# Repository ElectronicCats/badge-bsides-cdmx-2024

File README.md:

# Badge bsides CDMX 2024

## Getting started

1. Connect Badge via USB to your computer.
2. Open the serial port indicated for the badge on your computer through a program such as Arduino IDE, Putty or Screen at 115200 bauds.
3. The badge text should appear in the terminal.

## Tecnologia

- ESP32C6
- Neopixel LEDs
- USB C
- Display OLED
- 2x AA Battery Holder
- Shitty Addon Connector

## Gratitude
Do you want to say thank you? Tag these companies on social networks and show them your badge, thanks to them it is possible

- [HSBC](https://www.hsbc.com.mx/)
- [ElectronicCats](https://electroniccats.com/)
- [Bsides CDMX](https://bsidescdmx.org/)

## License

Electronic Cats invests time and resources providing this open source design, please support Electronic Cats and open-source hardware by purchasing products from Electronic Cats!

Designed by Electronic Cats.

Hardware released under an CERN Open Hardware Licence v1.2. See the LICENSE_HARDWARE file for more information.

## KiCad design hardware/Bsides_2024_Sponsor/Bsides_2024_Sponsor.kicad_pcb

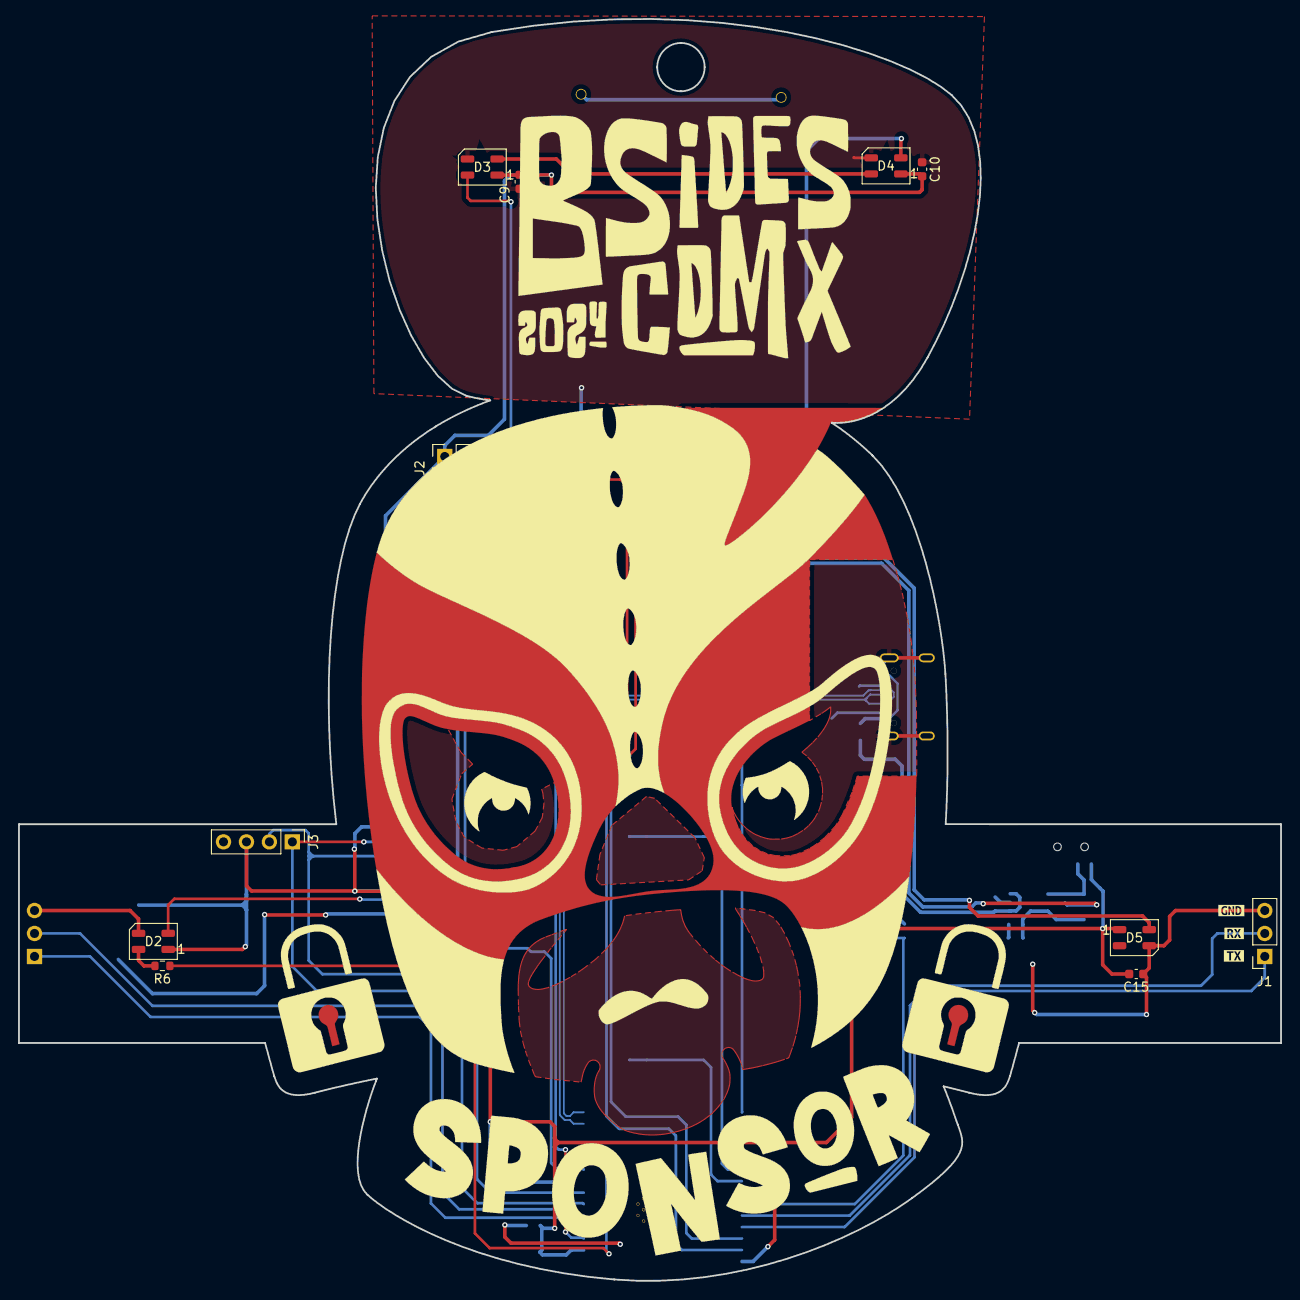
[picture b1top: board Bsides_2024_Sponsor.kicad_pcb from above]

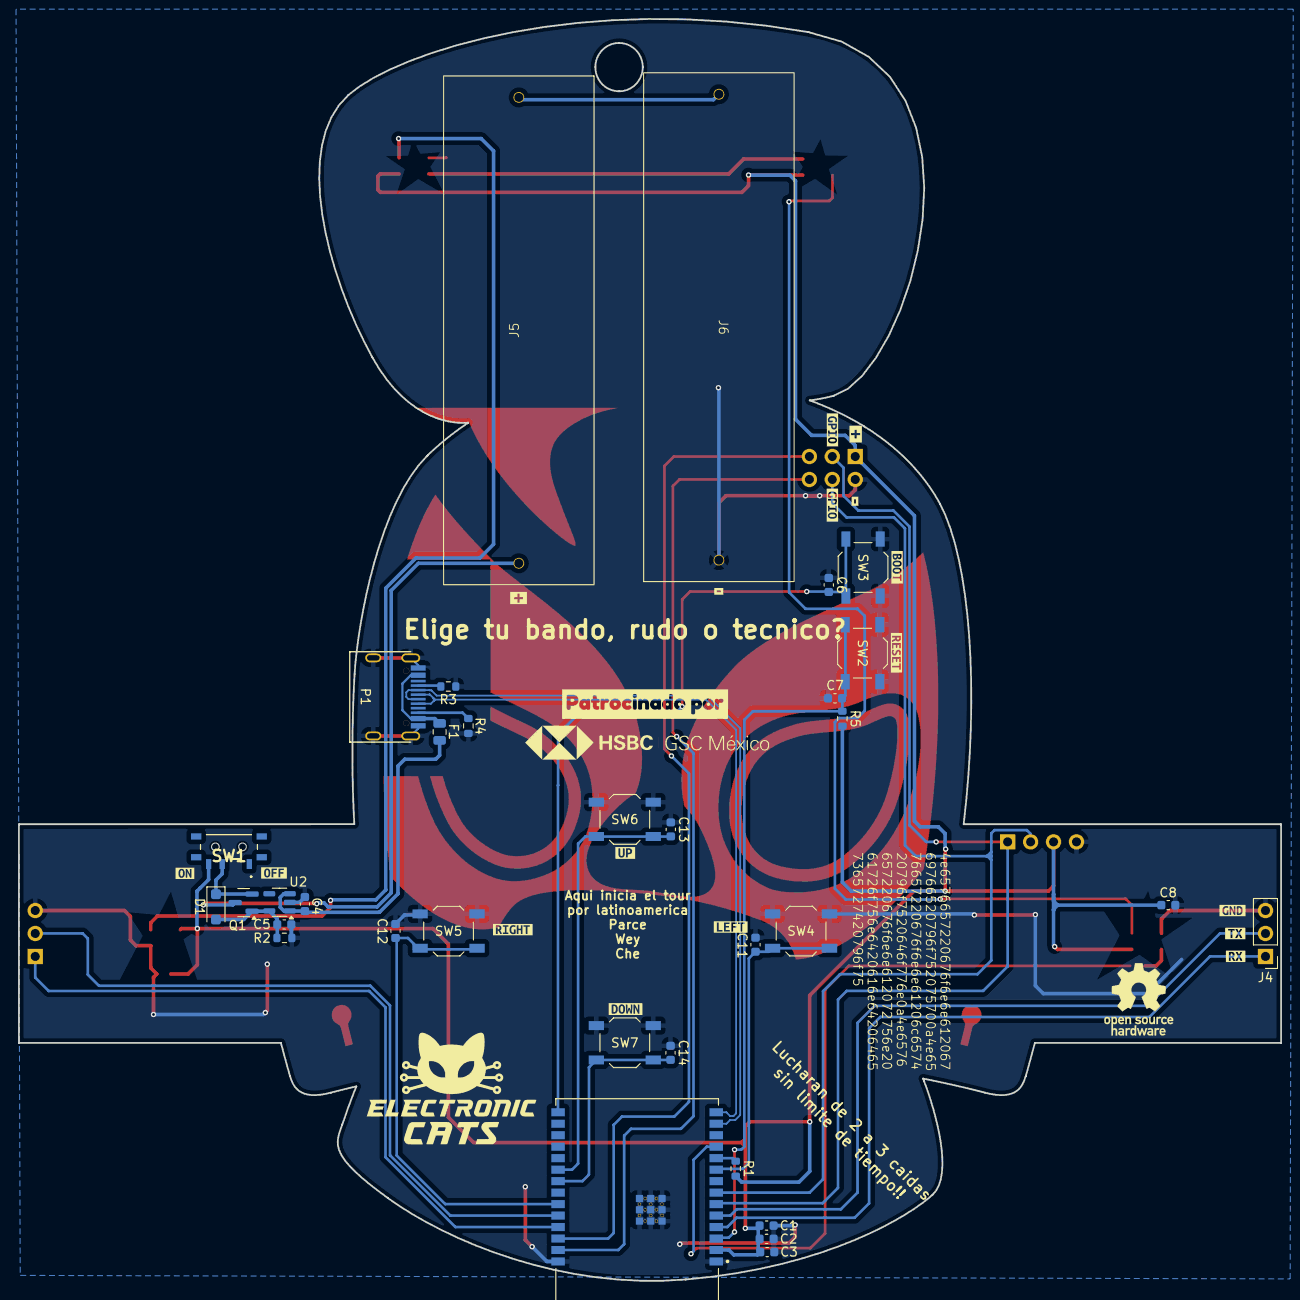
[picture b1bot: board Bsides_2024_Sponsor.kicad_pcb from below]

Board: 2 copper layers, 139.6 x 139.6 mm, 66 parts (51 on the bottom side), 32 nets.

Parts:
C1: 1uF; C_0603_1608Metric
C2, C3, C4, C5: 10uF; C_0603_1608Metric
C6, C7, C8, C9, C10, C11, C12, C13, C14, C15: 0.1uF; C_0603_1608Metric
D1: MBR120; D_SOD-123F
D2, D3, D4, D5: WS2812B; LED_WS2812B-Mini_PLCC4_3.5x3.5mm
F1: 0.75A; Fuse_0805_2012Metric
J1: Serial_IN; PinSocket_1x03_P2.54mm_Vertical
J2: Add_On; PinSocket_2x03_P2.54mm_Vertical
J3: OLED; Display OLED 128 x32
J4: Serial_OUT; PinHeader_1x03_P2.54mm_Vertical
J5, J6: Battery; BH-AA-A1AJ020
P1: USB_C_Plug_USB2.0; C393939
Q1: DMG3415U-7; SOT-23
R1: 3.3K; R_0603_1608Metric
R2: 100K; R_0603_1608Metric
R3, R4: 5k1; R_0603_1608Metric
R5: 10K; R_0603_1608Metric
R6: 470; R_0603_1608Metric
Ref**: Val**; Badge_Sponsor_Bsides_2024_CDMX
SW1: ON; MSK12C02
SW2, SW4, SW6: RESET; SW_SPST_TL3342
SW3: BOOT; SW_SPST_TL3342
SW5, SW7: SW_SPST_TL3342
U1: ESP32-C6-WROOM-1-N4; XCVR_ESP32-C6-WROOM-1-N8
U2: AP2112K-3.3; SOT-23-5
kibuzzard-666B5A62, kibuzzard-666B5A62#2: G***; kibuzzard-666B5A62
kibuzzard-666B5A91, kibuzzard-666B5A91#2: G***; kibuzzard-666B5A91
kibuzzard-666B5AA1, kibuzzard-666B5AA1#2: G***; kibuzzard-666B5AA1
kibuzzard-666B5BCA, kibuzzard-666B5BCA#2: G***; kibuzzard-666B5BCA
kibuzzard-666B5C0A, kibuzzard-666B5C0A#2: G***; kibuzzard-666B5C0A
kibuzzard-666B55CA: G***; kibuzzard-666B55CA
kibuzzard-666B327A: G***; kibuzzard-666B327A
kibuzzard-666B3243: G***; kibuzzard-666B3243
kibuzzard-666B3258: G***; kibuzzard-666B3258
kibuzzard-666C8E87: G***; kibuzzard-666C8E87
kibuzzard-666C63C4: G***; kibuzzard-666C63C4
kibuzzard-666C631C: G***; kibuzzard-666C631C
kibuzzard-666C633C: G***; kibuzzard-666C633C
kibuzzard-666C639C: G***; kibuzzard-666C639C
kibuzzard-666CA778: G***; kibuzzard-666CA778
kibuzzard-666CA782: G***; kibuzzard-666CA782

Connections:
+BATT: J5.2, Q1.3 (D)
/BOOT: C6.2, SW3.2, U1.15 (IO9)
/D+: P1.A6 (D+), U1.14 (IO13)
/D-: P1.A7 (D-), U1.13 (IO12)
/DOWN: C14.2, SW7.2, U1.21 (IO23)
/EN: C7.2, R5.1, SW2.2, U1.3 (EN)
/GPIO2: J2.6, U1.27 (IO2)
/GPIO3: J2.5, U1.26 (IO3)
/LEFT: C11.2, SW4.2, U1.9 (IO1)
/PIN: R6.1, U1.11 (IO10)
/RIGHT: C12.2, SW5.2, U1.23 (IO15)
/RX: J1.2, U1.24 (RXD0)
/RX1: J4.1, U1.4 (IO4)
/SCL: J2.4, J3.2, U1.7 (IO7)
/SDA: J2.3, J3.1, U1.6 (IO6)
/TX: J1.1, U1.25 (TXD0)
/TX1: J4.2, U1.5 (IO5)
/UP: C13.2, SW6.2, U1.20 (IO22)
/VOUT: C1.1, C2.1, C3.1, C8.2, C9.2, C10.2, C15.2, D2.1 (VDD), D3.1 (VDD), D4.1 (VDD), D5.1 (VDD), J2.1, J3.3, R1.2, R5.2, SW1.3 (A), U1.2 (3V3)
GND: C1.2, C2.2, C3.2, C4.2, C5.2, C6.1, C7.1, C8.1, C9.1, C10.1, C11.1, C12.1, C13.1, C14.1, C15.1, D2.3 (VSS), D3.3 (VSS), D4.3 (VSS), D5.3 (VSS), J1.3, J2.2, J3.4, J4.3, J6.1, P1.A1 (GND), P1.S1 (SHIELD), R2.2, R3.1, R4.1, SW2.1, SW3.1, SW4.1, SW5.1, SW6.1, SW7.1, U1.1 (GND), U1.28 (GND), U1.29 (GND), U1.30 (GND), U1.31 (GND), U1.32 (GND), U1.33 (GND), U1.34 (GND), U1.35 (GND), U1.36 (GND), U1.37 (GND), U2.2 (GND)
unnamed: C5.1, D1.2 (A), Q1.1 (G), R2.1, U2.5 (VOUT)
unnamed: D1.1 (K), Q1.2 (S), SW1.2 (B)
unnamed: D2.4 (DIN), R6.2
unnamed: D2.2 (DOUT), D3.4 (DIN)
unnamed: D3.2 (DOUT), D4.4 (DIN)
unnamed: D4.2 (DOUT), D5.4 (DIN)
unnamed: F1.1, P1.A4 (VBUS)
unnamed: J5.1, J6.2
unnamed: P1.A5 (CC), R3.2
unnamed: P1.B5 (VCONN), R4.2
unnamed: R1.1, U1.10 (IO8)
VBUS: C4.1, F1.2, U2.1 (VIN), U2.3 (EN)

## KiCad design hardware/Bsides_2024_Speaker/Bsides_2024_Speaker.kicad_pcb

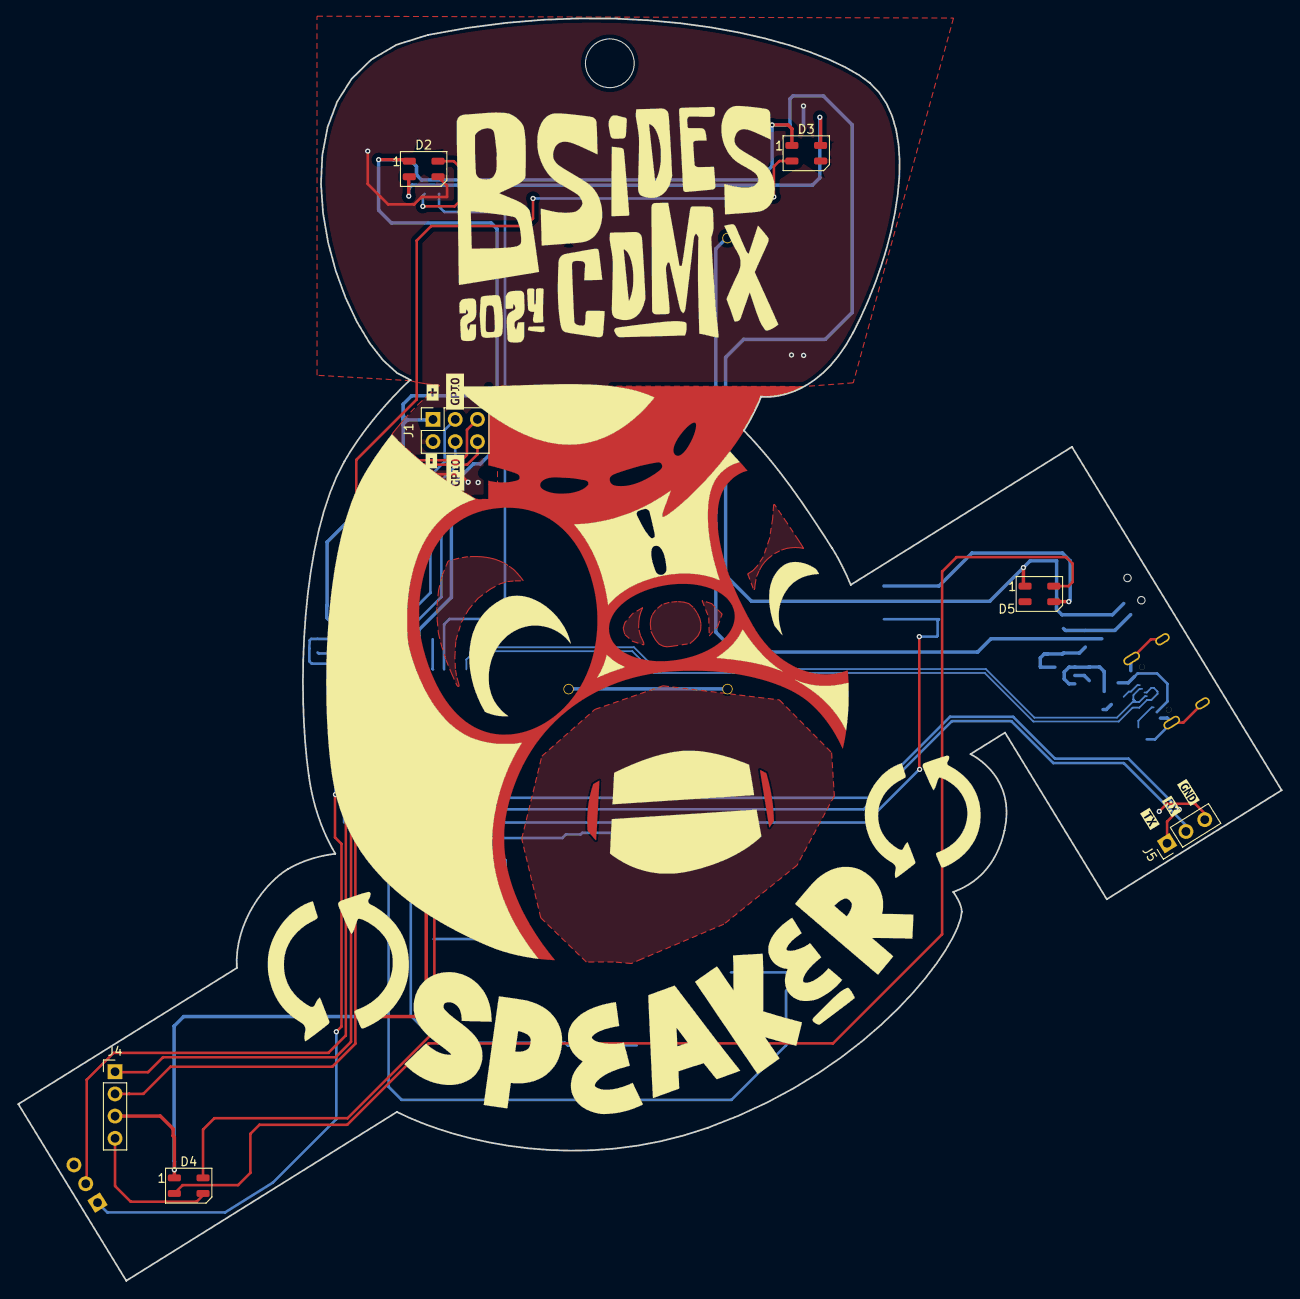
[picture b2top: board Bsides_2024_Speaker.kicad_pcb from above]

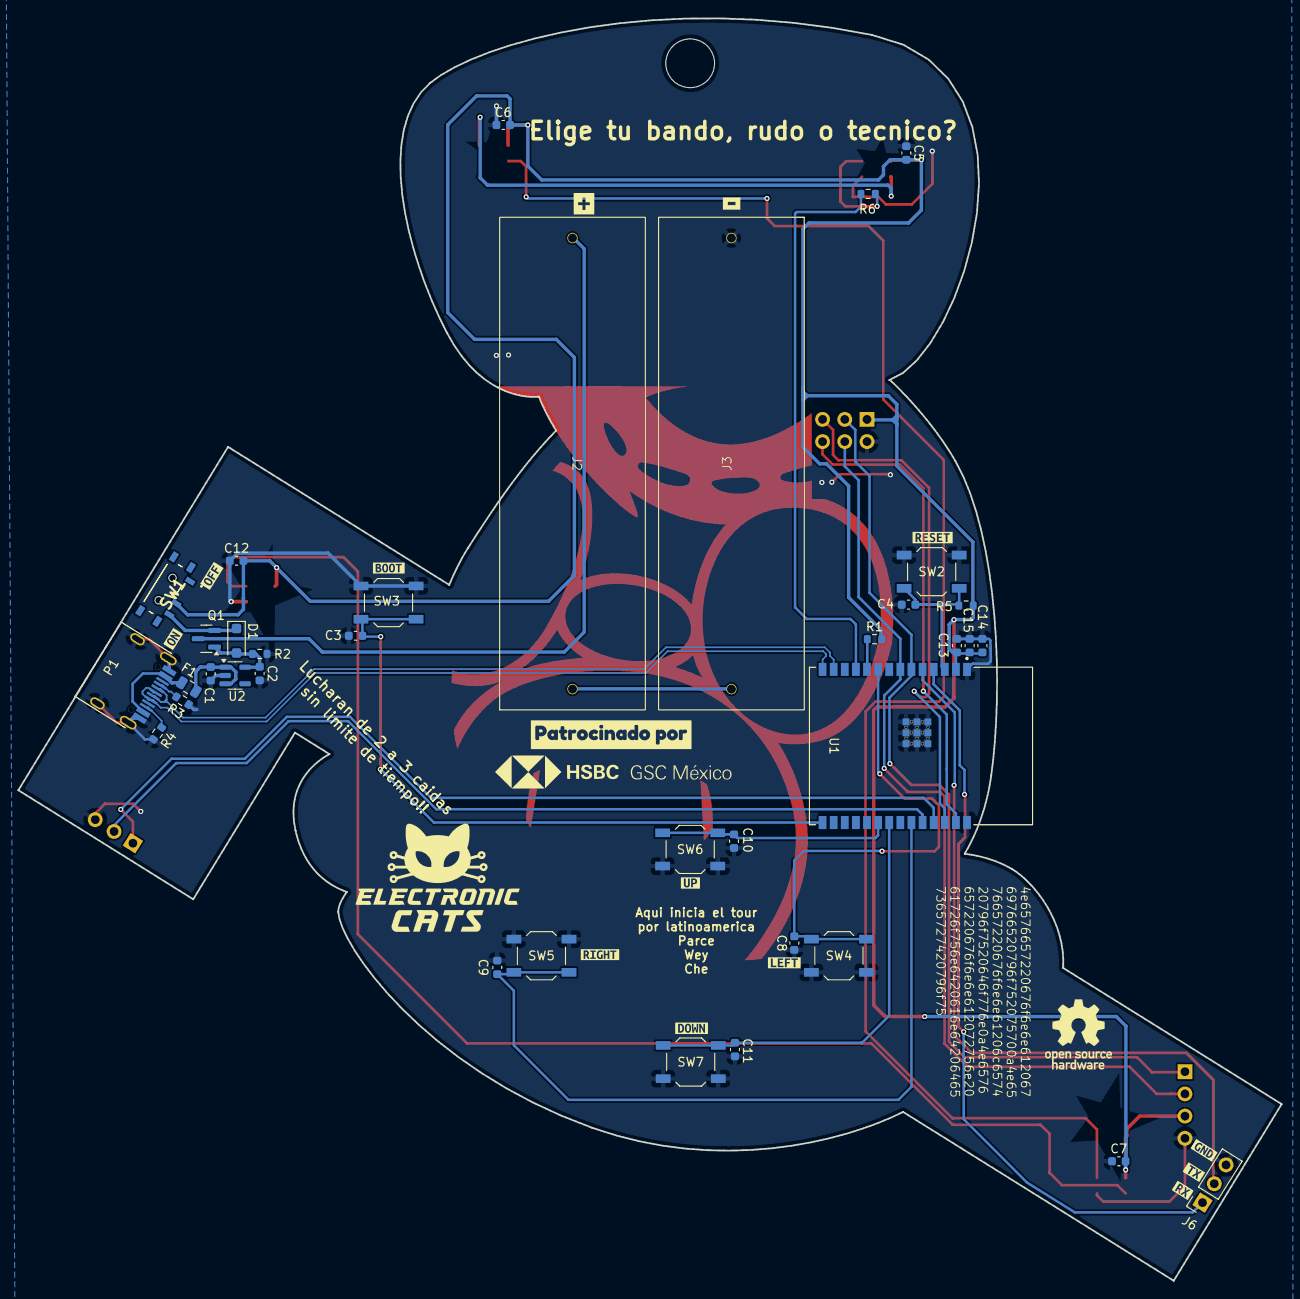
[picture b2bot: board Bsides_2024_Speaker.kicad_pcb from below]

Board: 2 copper layers, 144.4 x 144.3 mm, 66 parts (51 on the bottom side), 32 nets.

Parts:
C1, C2, C14, C15: 10uF; C_0603_1608Metric
C3, C4, C5, C6, C7, C8, C9, C10, C11, C12: 0.1uF; C_0603_1608Metric
C13: 1uF; C_0603_1608Metric
D1: MBR120; D_SOD-123F
D2, D3, D4, D5: WS2812B; LED_WS2812B-Mini_PLCC4_3.5x3.5mm
F1: 0.75A; Fuse_0805_2012Metric
J1: Add_On; PinSocket_2x03_P2.54mm_Vertical
J2, J3: Battery; BH-AA-A1AJ020
J4: OLED; Display OLED 128 x32
J5: Serial_IN; PinHeader_1x03_P2.54mm_Vertical
J6: Serial_OUT; PinSocket_1x03_P2.54mm_Vertical
P1: USB_C_Plug_USB2.0; C393939
Q1: DMG3415U-7; SOT-23
R1: 3.3K; R_0603_1608Metric
R2: 100K; R_0603_1608Metric
R3, R4: 5k1; R_0603_1608Metric
R5: 10K; R_0603_1608Metric
R6: 470; R_0603_1608Metric
Ref**: Val**; Badge_Speaker_Bsides_2024_CDMX
SW1: ON; MSK12C02
SW2, SW4, SW5, SW6, SW7: SW; SW_SPST_TL3342
SW3: BOOT; SW_SPST_TL3342
U1: ESP32-C6-WROOM-1-N4; XCVR_ESP32-C6-WROOM-1-N8
U2: AP2112K-3.3; SOT-23-5
kibuzzard-666B5A62, kibuzzard-666B5A62#2: G***; kibuzzard-666B5A62
kibuzzard-666B5A91, kibuzzard-666B5A91#2: G***; kibuzzard-666B5A91
kibuzzard-666B5AA1, kibuzzard-666B5AA1#2: G***; kibuzzard-666B5AA1
kibuzzard-666B5BCA: G***; kibuzzard-666B5BCA
kibuzzard-666B55CA: G***; kibuzzard-666B55CA
kibuzzard-666B311C: G***; kibuzzard-666B311C
kibuzzard-666B316E: G***; kibuzzard-666B316E
kibuzzard-666B327A: G***; kibuzzard-666B327A
kibuzzard-666B328D: G***; kibuzzard-666B328D
kibuzzard-666B558C: G***; kibuzzard-666B558C
kibuzzard-666B3243: G***; kibuzzard-666B3243
kibuzzard-666B3258: G***; kibuzzard-666B3258
kibuzzard-666C8A00: G***; kibuzzard-666C8A00
kibuzzard-666C8A1B: G***; kibuzzard-666C8A1B
kibuzzard-666C8A24: G***; kibuzzard-666C8A24
kibuzzard-666C8A46: G***; kibuzzard-666C8A46
kibuzzard-666C8E87: G***; kibuzzard-666C8E87
kibuzzard-666C89F7: G***; kibuzzard-666C89F7

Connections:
+BATT: J2.2, Q1.3 (D)
/BOOT: C3.2, SW3.2, U1.15 (IO9)
/D+: P1.A6 (D+), U1.14 (IO13)
/D-: P1.A7 (D-), U1.13 (IO12)
/DOWN: C11.2, SW7.2, U1.21 (IO23)
/EN: C4.2, R5.1, SW2.2, U1.3 (EN)
/GPIO2: J1.6, U1.27 (IO2)
/GPIO3: J1.5, U1.26 (IO3)
/LEFT: C8.2, SW4.2, U1.9 (IO1)
/PIN: R6.1, U1.11 (IO10)
/RIGHT: C9.2, SW5.2, U1.23 (IO15)
/RX: J5.2, U1.24 (RXD0)
/RX1: J6.1, U1.4 (IO4)
/SCL: J1.4, J4.2, U1.7 (IO7)
/SDA: J1.3, J4.1, U1.6 (IO6)
/TX: J5.1, U1.25 (TXD0)
/TX1: J6.2, U1.5 (IO5)
/UP: C10.2, SW6.2, U1.20 (IO22)
/VOUT: C5.2, C6.2, C7.2, C12.2, C13.1, C14.1, C15.1, D2.1 (VDD), D3.1 (VDD), D4.1 (VDD), D5.1 (VDD), J1.1, J4.3, R1.2, R5.2, SW1.2 (B), U1.2 (3V3)
GND: C1.2, C2.2, C3.1, C4.1, C5.1, C6.1, C7.1, C8.1, C9.1, C10.1, C11.1, C12.1, C13.2, C14.2, C15.2, D2.3 (VSS), D3.3 (VSS), D4.3 (VSS), D5.3 (VSS), J1.2, J3.1, J4.4, J5.3, J6.3, P1.A1 (GND), P1.S1 (SHIELD), R2.2, R3.1, R4.1, SW2.1, SW3.1, SW4.1, SW5.1, SW6.1, SW7.1, U1.1 (GND), U1.28 (GND), U1.29 (GND), U1.30 (GND), U1.31 (GND), U1.32 (GND), U1.33 (GND), U1.34 (GND), U1.35 (GND), U1.36 (GND), U1.37 (GND), U2.2 (GND)
unnamed: C2.1, D1.2 (A), Q1.1 (G), R2.1, U2.5 (VOUT)
unnamed: D1.1 (K), Q1.2 (S), SW1.3 (A)
unnamed: D2.4 (DIN), R6.2
unnamed: D2.2 (DOUT), D3.4 (DIN)
unnamed: D3.2 (DOUT), D4.4 (DIN)
unnamed: D4.2 (DOUT), D5.4 (DIN)
unnamed: F1.1, P1.A4 (VBUS)
unnamed: J2.1, J3.2
unnamed: P1.A5 (CC), R3.2
unnamed: P1.B5 (VCONN), R4.2
unnamed: R1.1, U1.10 (IO8)
VBUS: C1.1, F1.2, U2.1 (VIN), U2.3 (EN)

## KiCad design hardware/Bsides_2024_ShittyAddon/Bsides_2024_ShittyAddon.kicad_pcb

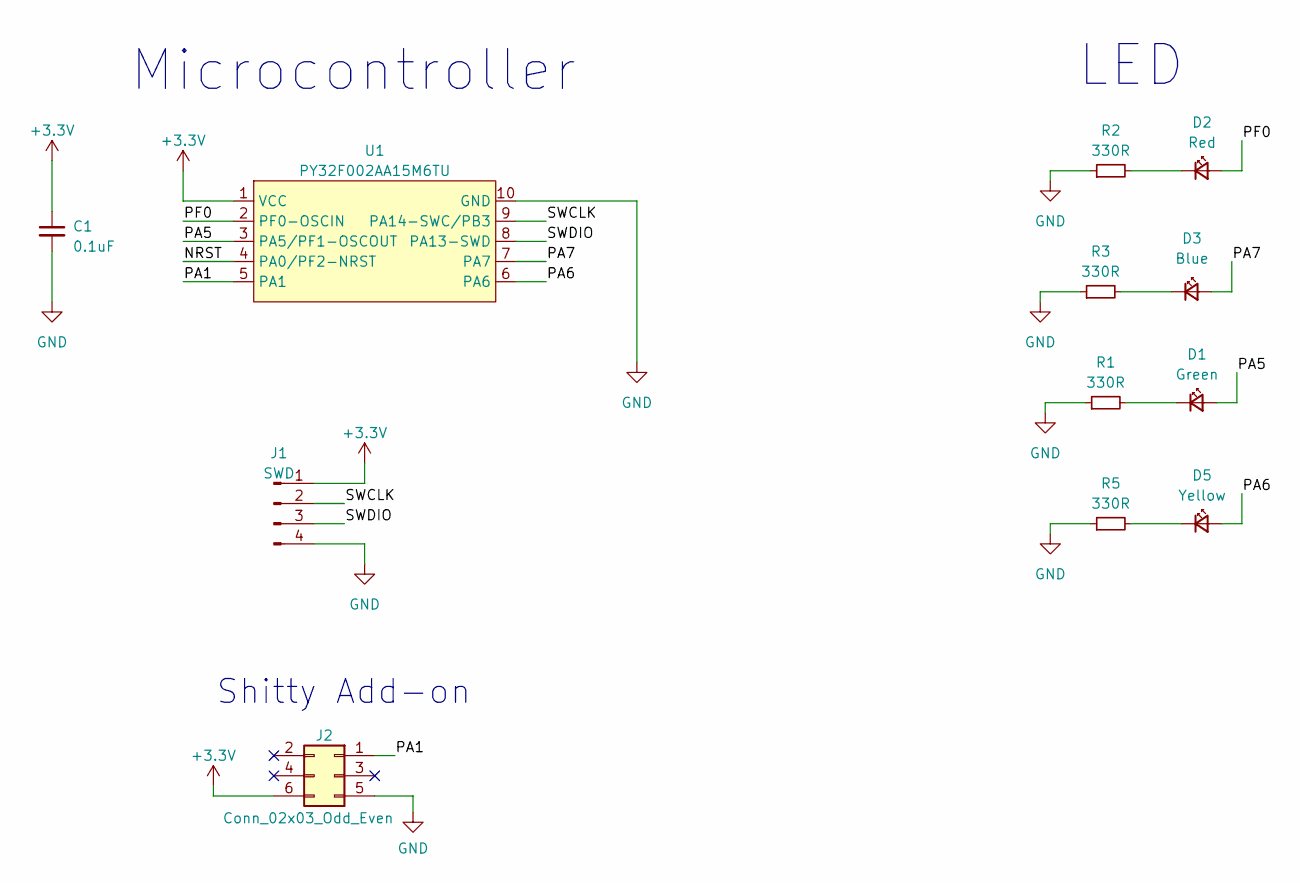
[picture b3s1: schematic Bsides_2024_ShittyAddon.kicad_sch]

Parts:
C1: 0.1uF; C_0805_2012Metric; LCSC# C282732
D1: Green; LED_0805_2012Metric; LCSC# C965815
D2: Red; LED_0805_2012Metric; LCSC# C965812
D3: Blue; LED_0805_2012Metric; LCSC# C205441
D5: Yellow; LED_0805_2012Metric; LCSC# C84261
J1: SWD; PinHeader_1x04_P2.54mm_Vertical
J2: Conn_02x03_Odd_Even; B-2100N06P-B111_CKM; LCSC# C706893
R1, R2, R3, R5: 330R; R_0805_2012Metric; LCSC# C2907321
U1: PY32F002AA15M6TU; PY32F002AA15M; LCSC# C5292058

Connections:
+3.3V: C1.1, J1.1, J2.6, U1.1 (VCC)
/NRST: U1.4 (PA0/PF2-NRST)
/PA1: J2.1, U1.5 (PA1)
/PA5: D1.2 (A), U1.3 (PA5/PF1-OSCOUT)
/PA6: D5.2 (A), U1.6 (PA6)
/PA7: D3.2 (A), U1.7 (PA7)
/PF0: D2.2 (A), U1.2 (PF0-OSCIN)
/SWCLK: J1.2, U1.9 (PA14-SWC/PB3)
/SWDIO: J1.3, U1.8 (PA13-SWD)
GND: C1.2, J1.4, J2.5, R1.1, R2.1, R3.1, R5.1, U1.10 (GND)
unnamed: D1.1 (K), R1.2
unnamed: D2.1 (K), R2.2
unnamed: D3.1 (K), R3.2
unnamed: D5.1 (K), R5.2

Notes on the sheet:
Microcontroller
Shitty Add-on
LED

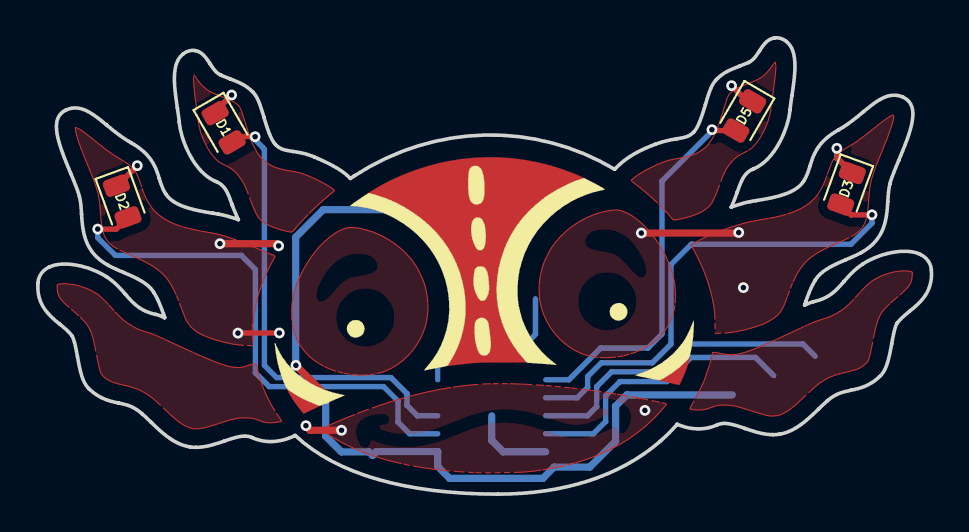
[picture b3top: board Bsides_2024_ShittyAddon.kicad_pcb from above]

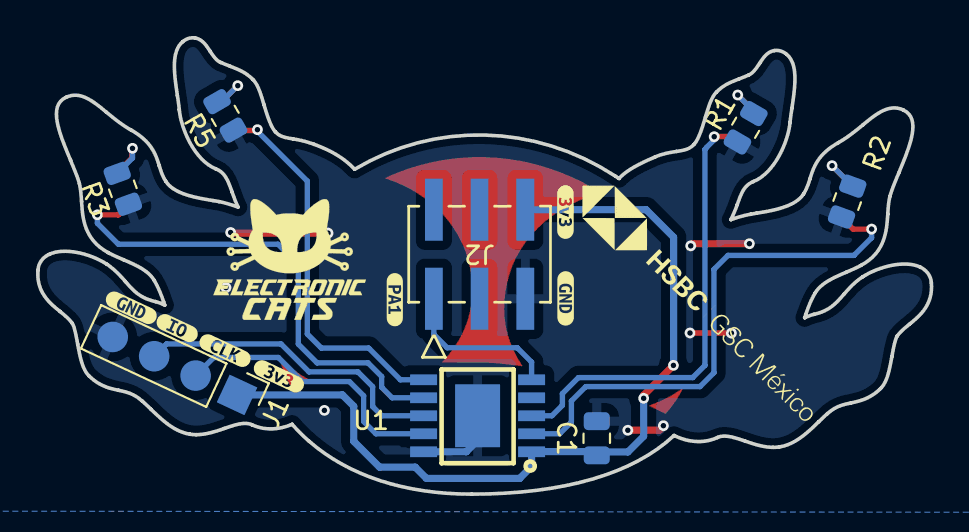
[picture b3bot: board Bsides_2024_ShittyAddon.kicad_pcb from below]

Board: 2 copper layers, 49.7 x 25.4 mm, 20 parts (15 on the bottom side), 13 nets.

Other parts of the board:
Ref**: Val**; Ajolote-bsidescdmx_A
kibuzzard-666C77E0, kibuzzard-666C77E0#2: G***; kibuzzard-666C77E0
kibuzzard-666C787C: G***; kibuzzard-666C787C
kibuzzard-666C7809, kibuzzard-666C7809#2: G***; kibuzzard-666C7809
kibuzzard-666C7823: G***; kibuzzard-666C7823
kibuzzard-666C7874: G***; kibuzzard-666C7874

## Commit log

2024-04-16 feat(Hw):Init_Schematic
2024-04-23 feat(Hw):Added_LED´s_Buttons
2024-04-27 fix(Hw):Changed_raspberry
2024-04-29 feat(hw): add labels schematic
2024-05-07 feat(Hw):Add_Guest_Sponsor_Community_Staff
2024-05-09 feat(Hw):Update_Staff_PCB
2024-05-10 feat(Hw):Init_Floorplan
2024-05-10 feat(Hw):Add_Preview
2024-05-11 feat(Hw):Added_Guest_And_Sponsor_Floorplan_and_3d_Models
2024-05-11 feat(Hw):Update_3d_Model
2024-05-13 feat(Hw):Added_speaker_Badge_Floorplan
2024-05-15 feat: Update README.md
2024-05-20 feat(Hw): Shitty Addon PCB added
2024-05-22 feat(Hw): Start new floorplan
2024-05-27 feat(Hw): Update PCB
2024-05-28 feat(Hw):Update_Route_Speaker
2024-05-28 feat(Hw):Update_PCB_Speaker
2024-05-29 feat(Hw):Update_Floorplan_Sponsor
2024-05-30 feat:(Hw)Update_PCB_Speaker_Sponsor_Staff
2024-06-04 feat(Hw): Update PCB and schematic
2024-06-10 feat: add minino firmware
2024-06-11 First_Route_Speaker
2024-06-11 Revert "Merge branch 'main' of https://github.com/ElectronicCats/badge-bsides-cdmx-2024"
    This reverts commit 844f9cf1141b02d246949023f3a5d84c3d1d6870, reversing
    changes made to df45190e2e7c4c17babbd6f5b24a18277498f0c6.
2024-06-11 feat: adapt interface to 128x32
2024-06-11 feat(Hw): Update schematics
2024-06-11 feat(Hw):Update_Sch_Speaker
2024-06-11 feat(Hw): Update route
2024-06-11 feat(Hw):Update_Staff_Sch_And_PCB
2024-06-12 feat(Hw):First_Route_Staff
2024-06-12 refactor: zboss woking from managed components
2024-06-12 Update route and schematic
2024-06-12 feat(Hw):Update_Route_Sponsor
2024-06-12 feat(Hw):Moved_Buttons_sponsor
2024-06-12 fet(Hw): Update route
2024-06-12 feat(Hw):Moved_Buttons_Speaker
2024-06-13 feat(Hw):Update_Csv_Speaker
2024-06-13 feat(Hw): Update BOM ShittyAddon
2024-06-13 Faet(Hw): Update BOM Speaker
2024-06-13 feat: lobby manager example
2024-06-13 feat(Hw):Update_BOM_Added_Labels
2024-06-13 feat(Hw): Update BOM
2024-06-13 feat(Hw): Update route Speaker and Sponsor
2024-06-14 feat(Hw): Update route Community
2024-06-14 feat(Hw): Labels added
2024-06-14 feat(Hw): Update labels
2024-06-14 feat(Hw):Update_PCB_Community
2024-06-14 feat(Hw):Moved_Battery_Case
2024-06-14 feat(Hw):Update_Guest_SCH_Labels
2024-06-14 feat(Hw):Update_Shitty_Add_On
2024-06-14 feat(Hw): Update schematic and route
2024-06-14 feat(Hw): Update .step
2024-06-14 feat(Hw):Update_Labels_SCH_PCB_Sponsor_And_Staff
2024-06-14 feat(Hw): Move labels
2024-06-14 feat(hw): add labels and logos speaker
2024-06-14 feat: Add games option in menu screens
2024-06-14 feat(hw): add logos staff
2024-06-14 feat(hw): logos sponsor
2024-06-14 feat(hw): add logos guest
2024-06-14 feat(hw): add logos community
2024-06-14 feat(hw): add labels
2024-06-14 feat(hw): add logos shitty addon
2024-06-14 feat(Hw):Update_footprint_badge
2024-06-14 feat(Hw): Update label ShittyAddon
2024-06-14 feat: lobby manager initialized from GUI & deinit added to lobby manager & badge connect
2024-06-15 feat: physical badge connections as conditional for game connection
2024-06-18 refactor: zigbee toggle button & ble spam & wifi deauth bitmaps resized
2024-06-18 refactor: resize of wifi & zigbee bitmaps
2024-06-19 feat: Implement send uart packet
    - Send UART packet
    - Change Zigbee module
    - Add loop menu options
    Note: Bad FCS, requires check the calculation function
2024-06-19 feat: Implement unlock ajolote
2024-06-19 feat: Ajolote animation
    - Fix init logo
2024-06-20 feat: Init DOS
2024-06-20 refactor: add badge connect as a dependency
2024-06-21 feat: handle disconnection events & display events callbacks added
2024-06-21 feat: Implement Wifi config
2024-06-24 fix: badge connect failed to start
2024-06-24 feat: rope game test
2024-06-25 feat: ping attempts implemented
    Forced to be host on lobby manager
2024-06-25 feat: game start from host cmd
2024-06-25 feat: game stops from host
2024-06-25 fix: game exit bug
2024-06-26 feat: DOS app
    - Changes apps
    - Ajo module
2024-06-26 feat: Merge badge connect
2024-06-26 feat: Labels
2024-06-26 fix: add games begin in menu screens module
2024-06-26 feat: create a bar bitmap
2024-06-26 feat(Fw): ShittyAddon firmware added
2024-06-26 chore: remove clean
2024-06-26 chore: enable log master level
2024-06-27 feat: game over event & send game update fixed
2024-06-27 chore: add temporarily lck files
2024-06-27 chore: add configuration rules for minino and badges pins
2024-06-28 refactor: rope game UI
2024-06-28 refactor: lobby UI & games module
2024-06-28 feat: physical connection for lobby manager
2024-06-28 refactor: rope bitmaps
2024-06-28 refactor: lobby manager ping
2024-06-28 feat: badge connect animation slowed
2024-07-01 feat: game start cmd redundancy
2024-07-01 chore: use v1.0.0 of badge connect
2024-07-01 fix: death now able to show ssid
2024-07-01 fix: avoid leds on software reset
2024-07-01 fix: free memory in menu screens modules
2024-07-01 fix: bsides logo
2024-07-01 feat: add promiscuous functions to open thread
2024-07-01 feat: add open thread broadcast app
2024-07-01 docs: add physical connection instructions
2024-07-02 feat: remove gps and matter menus
2024-07-02 feat: add dragonjar logo
2024-07-02 feat: add ekoparty logo
2024-07-02 feat: add bugcon logo
2024-07-02 feat: order players strenght
2024-07-02 fix: games module exit
2024-07-02 refactor: open game changed
2024-07-02 feat: add badge link menu
2024-07-03 feat: display hsbc logo at startup
2024-07-03 feat: update credits text
    - add sponsors
    - add hardware designers
    - add firmware developers
2024-07-03 chore: replace minino with this badge
2024-07-03 fix: next and prev menu tables size
2024-07-03 feat: lobby manager inactive while playing
2024-07-04 feat: screens
2024-07-04 fix: avoid development banner on Games menu
2024-07-04 feat: improve UI on rope game
2024-07-04 feat: CTF BLE
2024-07-04 feat: Remove led_function
2024-07-04 feat: detect no bsides badges
2024-07-04 chore: remove examples
2024-07-05 feat: Speed bags
2024-07-05 feat: Game 5vs5
2024-07-05 feat: arrow aiming to my strenght value
2024-07-05 feat: add optional env variable to badge_connect_src
2024-07-05 feat: Fix bitmaps
2024-07-06 feat: add loading bar at scanning
2024-07-06 fix: second badge not detected
2024-07-06 refactor: id var name changed
2024-07-06 feat: add rssi filter
2024-07-08 feat: client screen updated
2024-07-08 feat: display logo of found badge
2024-07-08 feat: show dos menu after found badge
2024-07-08 feat: game over shows winner and losser
2024-07-08 feat: Game
2024-07-08 feat: add get build script
2024-07-08 feat: arm wretstling game
2024-07-08 feat: Logs
2024-07-08 refactor: code rearrangement
2024-07-09 fix: set bsides badge
2024-07-09 feat: add neopixels api
2024-07-09 refactor: soft reset
2024-07-09 feat: software reset in badge link & wifi modules
2024-07-09 feat: buzzer sound on startup
2024-07-09 feat: remove zigbee light menu
2024-07-09 feat: arm wrestling game update
2024-07-09 fix: infinite items scroll on startup & wifi module
2024-07-10 feat: add mutex in oled module
2024-07-10 feat: Fixing DOS
2024-07-10 refactor: thread broadcast screen
2024-07-10 refactor: replace uart to jtag config for esp console
2024-07-10 feat: Change names
2024-07-10 refactor: change badge link help to spanish
2024-07-10 docs: add developer guide
2024-07-10 feat: add games help menus
2024-07-10 refactor: rope game help translated to spanish
2024-07-10 feat: Translate
2024-07-10 feat: using neopixels in rope game
2024-07-10 feat: Add Pocho soporte
2024-07-10 refactor: rope game & games module translated
2024-07-11 refactor: Neopixel brightness reduced on rope game
2024-07-11 refactor: brigthness reduced to 50
2024-07-11 feat: Ajolotin & LEDS
2024-07-11 refactor: translate badge link feature to spanish
2024-07-11 feat: compress build files with get build script
2024-07-11 feat: Improve time reset
2024-07-11 fix: remove wifi sniffer settings menu
2024-07-11 docs: fix git clone link
2024-07-11 feat: Fix bugs
2024-07-11 feat: added arm game data function
2024-07-12 fix: update strength value on screen
2024-07-12 fix: game over screen
2024-07-12 feat: Start CTF BLE Screens
2024-07-12 feat: Remove DOS from menu
2024-07-12 refactor: zb switch labels
2024-07-12 feat: settings menus removed
2024-07-12 feat: using neopixels in arm game
2024-07-12 fix: Games help stuff
2024-07-12 refactor: Bt Spam animation task removed
2024-07-12 feat: neopixels scanning animation test
2024-07-12 feat: NEOPIXELS and Screens
2024-07-12 fix: display attacks & details in deauth
2024-07-12 refactor: leds replaced by neopixels
2024-07-12 refactor: lobby UI improved
2024-07-12 refactor: rope game UI improved
2024-07-12 feat: wifi animations
2024-07-12 fix: team asign
2024-07-12 feat: Wifi Screens
2024-07-13 feat: Remove bypass
2024-07-13 feat: Exit zigbee
2024-07-13 feat: Add Vencidad manual
2024-07-13 feat: Fix Vencidas help
2024-07-13 feat: Add display MAC
2024-07-15 feat: Create LICENSE
2024-07-15 feat: Create LICENSE_HARDWARE.md
2024-07-15 feat: Clean screen
